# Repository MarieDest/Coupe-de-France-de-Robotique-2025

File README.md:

# Coupe-de-France-de-Robotique-2025
repo pour le code robot pour la coupe de France de robotique 2025

Cette année, l'idée est de passer sur ST, pour la carte principale et pour un des moyens de détection.

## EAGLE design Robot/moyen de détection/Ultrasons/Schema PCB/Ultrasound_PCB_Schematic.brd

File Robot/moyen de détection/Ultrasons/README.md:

partie liée au moyen de détection à Ultrason. 

Une vidéo explicative est disponible sur Youtube.

https://www.youtube.com/watch?v=CBb2TiV3mDs

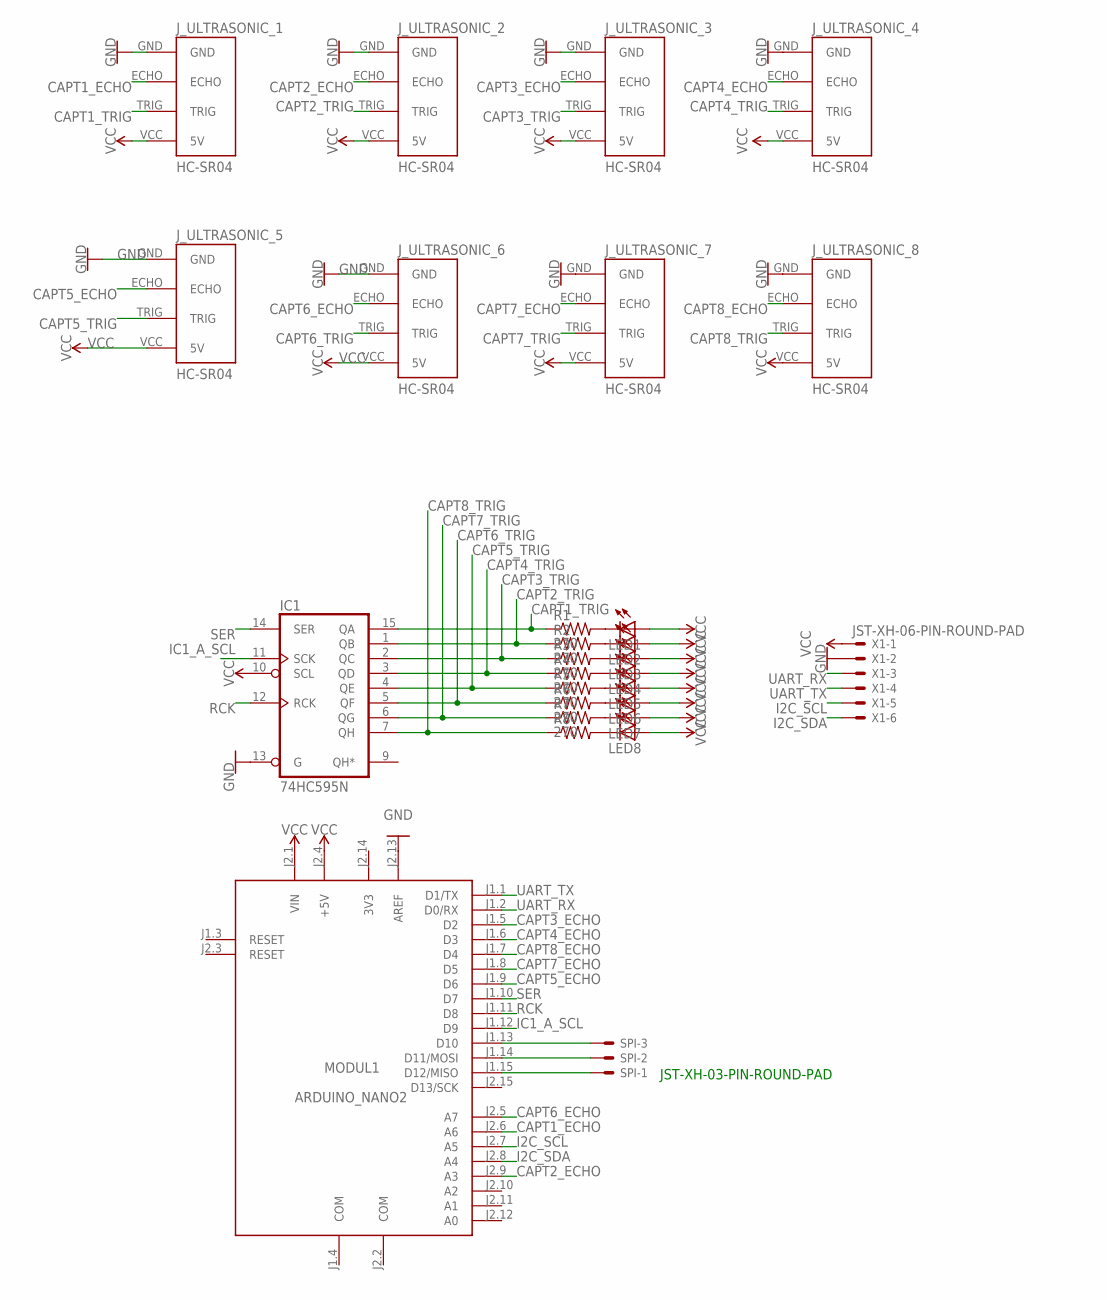
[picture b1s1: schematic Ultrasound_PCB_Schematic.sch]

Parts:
IC1: 74HC595N; DIL16
J_ULTRASONIC_1, J_ULTRASONIC_2, J_ULTRASONIC_3, J_ULTRASONIC_4, J_ULTRASONIC_5, J_ULTRASONIC_6, J_ULTRASONIC_7, J_ULTRASONIC_8: HC-SR04; HC-SR04_FOOTPRINT
LED1, LED2, LED3, LED4, LED5, LED6, LED7, LED8: LED5MM
MODUL1: ARDUINO_NANO2
R1, R2, R3, R4, R5, R6, R7: 270; 0207/5V
R8: R-US_0207/5V; 0207/5V
SPI: JST-XH-03-PIN-ROUND-PAD; JST-XH-03-PACKAGE-ROUND-PAD
X1: JST-XH-06-PIN-ROUND-PAD; JST-XH-06-PACKAGE-ROUND-PAD

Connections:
3V3: MODUL1.J2.14 (3V3)
CAPT1_ECHO: J_ULTRASONIC_1.ECHO, MODUL1.J2.6 (A6)
CAPT1_TRIG: IC1.15 (QA), J_ULTRASONIC_1.TRIG, R1.1
CAPT2_ECHO: J_ULTRASONIC_2.ECHO, MODUL1.J2.9 (A3)
CAPT2_TRIG: IC1.1 (QB), J_ULTRASONIC_2.TRIG, R2.1
CAPT3_ECHO: J_ULTRASONIC_3.ECHO, MODUL1.J1.5 (D2)
CAPT3_TRIG: IC1.2 (QC), J_ULTRASONIC_3.TRIG, R3.1
CAPT4_ECHO: J_ULTRASONIC_4.ECHO, MODUL1.J1.6 (D3)
CAPT4_TRIG: IC1.3 (QD), J_ULTRASONIC_4.TRIG, R4.1
CAPT5_ECHO: J_ULTRASONIC_5.ECHO, MODUL1.J1.9 (D6)
CAPT5_TRIG: IC1.4 (QE), J_ULTRASONIC_5.TRIG, R5.1
CAPT6_ECHO: J_ULTRASONIC_6.ECHO, MODUL1.J2.5 (A7)
CAPT6_TRIG: IC1.5 (QF), J_ULTRASONIC_6.TRIG, R6.1
CAPT7_ECHO: J_ULTRASONIC_7.ECHO, MODUL1.J1.8 (D5)
CAPT7_TRIG: IC1.6 (QG), J_ULTRASONIC_7.TRIG, R7.1
CAPT8_ECHO: J_ULTRASONIC_8.ECHO, MODUL1.J1.7 (D4)
CAPT8_TRIG: IC1.7 (QH), J_ULTRASONIC_8.TRIG, R8.1
COM: MODUL1.J1.4 (COM), MODUL1.J2.2 (COM)
GND: IC1.8 (GND), IC1.13 (G), J_ULTRASONIC_1.GND, J_ULTRASONIC_2.GND, J_ULTRASONIC_3.GND, J_ULTRASONIC_4.GND, J_ULTRASONIC_5.GND, J_ULTRASONIC_6.GND, J_ULTRASONIC_7.GND, J_ULTRASONIC_8.GND, MODUL1.J2.13 (AREF), X1.2
I2C_SCL: MODUL1.J2.7 (A5), X1.5
I2C_SDA: MODUL1.J2.8 (A4), X1.6
IC1_A_SCL: IC1.11 (SCK), MODUL1.J1.12 (D9)
unnamed: LED8.K (C), R8.2
unnamed: LED7.K (C), R7.2
unnamed: LED6.K (C), R6.2
unnamed: LED5.K (C), R5.2
unnamed: LED4.K (C), R4.2
unnamed: MODUL1.J1.15 (D12/MISO), SPI.1
unnamed: MODUL1.J1.14 (D11/MOSI), SPI.2
unnamed: MODUL1.J1.13 (D10), SPI.3
unnamed: LED3.K (C), R3.2
unnamed: LED2.K (C), R2.2
unnamed: LED1.K (C), R1.2
RCK: IC1.12 (RCK), MODUL1.J1.11 (D8)
SER: IC1.14 (SER), MODUL1.J1.10 (D7)
UART_RX: MODUL1.J1.2 (D0/RX), X1.3
UART_TX: MODUL1.J1.1 (D1/TX), X1.4
VCC: IC1.10 (SCL), IC1.16 (VCC), J_ULTRASONIC_1.VCC (5V), J_ULTRASONIC_2.VCC (5V), J_ULTRASONIC_3.VCC (5V), J_ULTRASONIC_4.VCC (5V), J_ULTRASONIC_5.VCC (5V), J_ULTRASONIC_6.VCC (5V), J_ULTRASONIC_7.VCC (5V), J_ULTRASONIC_8.VCC (5V), LED1.A, LED2.A, LED3.A, LED4.A, LED5.A, LED6.A, LED7.A, LED8.A, MODUL1.J2.1 (VIN), MODUL1.J2.4 (+5V), X1.1

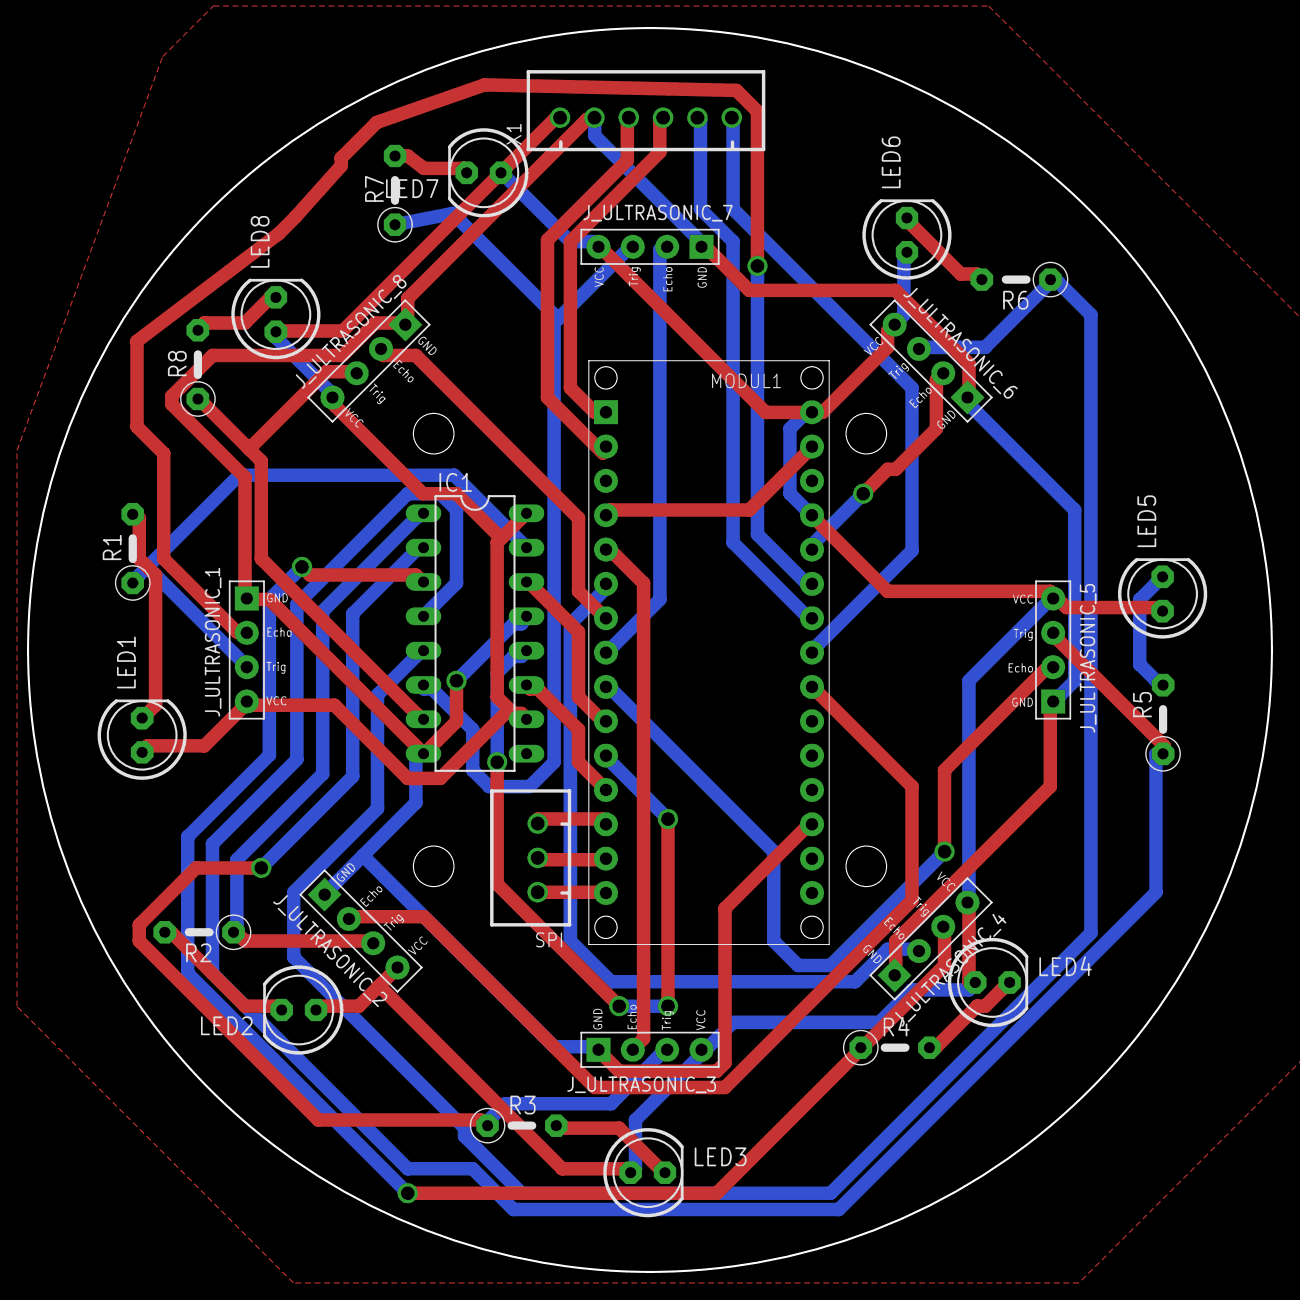
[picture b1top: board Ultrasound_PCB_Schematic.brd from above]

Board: 2 copper layers, 92.0 x 92.0 mm, 28 parts (0 on the bottom side), 37 nets.

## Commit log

2024-06-16 Ajout de la version 1 capteur VL53L1
    programme qui permet d'avoir 9 Capteurs TOF qui forme un Lidar fixe, suivant le projet de ST.
    https://www.st.com/en/embedded-software/stsw-img017.html#overview
    Programme qui fonctionne avec un capteur.
2024-09-22 PAMI MAJ
    codes pour le controle individuel du module bluetooth, des encodeurs et des moteurs. Dans le code de l'encodeur, le bouton et la tirete sont aussi testés.
2024-09-29 Update MotorTest.ino
    update avec une version qui fonctionne avec 2 moteurs. Alim 5V les moteurs tournent normalement. Alim 9V les moteurs tournent vite dans un sens et a bonne vitesse dans l'autre. il faudra peut etre es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
2025-03-01 éléments pour la vidéo balise Ultrason
    Ajout d'un dossier Ultrason, contenant le code Arduino et le schema de la carte PCB
2025-03-01 Ajout modèles 3D
    Ajout des STEP 3D des elements du moyen de détection Ultrason
2025-03-01 création d'un readme

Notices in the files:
parts and their libraries:
SparkFun-PowerSymbols: Licensing: Creative Commons ShareAlike 4.0 International - https://creativecommons.org/licenses/by-sa/4.0
